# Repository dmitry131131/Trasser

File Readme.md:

# Трассерная насадка для игры в страйкбол

## Содержание
1. [Цель проекта](#цель-проекта)
2. [Режимы работы](#режимы-работы)
3. [Принцип работы](#принцип-работы)
4. [Необходимые компоненты](#необходимые-компоненты)
5. [Используемые инструменты и станки](#используемые-инструменты-и-станки)
6. [Проблемы и трудности](#проблемы-и-трудности)
7. [Результат](#результат)

## Цель проекта

Разработка и изготовление компактной и надежной трассерной насадки для страйкбольного оружия, которая позволяет визуализировать полет шаров в условиях низкой освещенности. Насадка будет крепиться на ствол оружия на резьбу `M14-` и активироваться при выстреле, подсвечивая траекторию полета шаров с помощью ультрафиолетовых светодиодов. Управление устройством осуществляется на базе микроконтроллера `ATtiny13`, что обеспечивает минимальные габариты и энергопотребление.

## Режимы работы

Трассерная насадка будет иметь `3 режима` работы:
1. Ультрафиолетовая вспышка для подсветки шаров
2. Оранжевая вспышка на срезе ствола для имитации вспышки выстрела
3. Ультрафиолетовая вспышка и имитация вспышки выстрела

## Принцип работы

+ При выстреле страйкбольный шар проходит через ствол, пересекая луч инфракрасного датчика.
+ Датчик передает сигнал на микроконтроллер ATtiny13.
+ Микроконтроллер активирует ультрафиолетовые светодиоды на короткий промежуток времени (0.1 секунду).
+ Светодиоды подсвечивают шар внутри ствола, делая его видимым в темноте.
+ После завершения цикла устройство возвращается в режим ожидания для экономии энергии.

### Идейная схема реализации 

## Необходимые компоненты

Список необходимых компонентов:

### Электроника

| Компонент                         | Количество             |
|-----------------------------------|------------------------|
| Двухсторонний текстолит           | 100x100mm              |
| Микроконтроллер Attiny13          | 1шт                    |
| УФ светодиоды формата 5050        | 3шт                    |
| Оранжевые светодиоды 1206         | 3шт                    |
| SMD переменный резистор 20k       | 1шт                    |
| SMD резистор 0805 10k             | 1шт                    |
| SMD резистор 0805 1k              | 4шт                    |
| SMD резистор 0805 4k              | 1шт                    |
| SMD резистор 1206 20ОМ            | 2шт                    |
| SMD резистор 1206 150ОМ           | 1шт                    |
| SMD транзистор NPN bc817-40       | 2шт                    |
| SMD конденсатор 0603 0.1мкФ       | 2шт                    |
| SMD конденсатор 0603 10мкФ        | 1шт                    |
| Инфракрасный фотодиод 3мм         | 1шт                    |
| SMD инфракрасный светодиод        | 1шт                    |
| SMD светодиод 0603 красный        | 1шт                    |
| SMD светодиод 0603 синий          | 1шт                    |
| SMD микросхема TP4056             | 1шт                    |
| Li-ion аккумулятор 20/20/4мм 3.7В | 1шт                    |
| USB Type-C разъём                 | 1шт                    |
| SMD кнопка                        | 1шт                    |

### Корпус

| Компонент                         | Количество             |
|-----------------------------------|------------------------|
| Алюминиевая труба D = 35мм        | 60мм                   |
| Прозрачная трубка D = 15мм        | 60мм                   |
| Винты M3 15мм                     | 2шт                    |
| Круг алюминиевый Д16-Т D = 40мм   | 60мм                   |
| Прокладка диаметром 15мм          | 1шт                    |
| Круг алюминиевый D = 20мм         | 30мм                   |

## Используемые инструменты и станки

В этом проекте было задействовано следующее оборудование:

### Для изготовления корпуса

Для изготовления корпуса и переходника `M11/M14-` были использованы:

1. Токарно-винторезный станок `JET GHB-1340A DRO` - для токарных работ

2. Редукторный фрезерно-сверлильный станок `JET JMD-45LPFD` - для фрезерно-сверлильных работ

3. Ленточнопильный станок `JET MBS-1011DAP` - для отрезания заготовок

### Для изготовления электроники

1. Настольный фрезерно-гравировальный станок `Charly 4U` - для изготовления печатных плат

2. Осцилограф цифровой `UNI TREND UTD2102CM` - для диагностики схемы

3. Паяльная станция `Ersa i-CON1` с паяльником `i-TOOL 0IC1100A` - для сборки печатной платы

## Процесс изготовления

#### Измерение всех стыковочных параметров, таких как характерные габариты, толщина ствола и параметры резьбы.
  В результате этих измерений было установлено, что в качестве основной резьбы крепления насадки к стволу служит левая резьба стандарта М14 шаг 1мм
  Но в качестве дополнения для использования на стволе пистолета решено было добавить в комплект переходник с M14- на резьбу M11 шаг 1мм, потому что
  именно такую резьбу имеет ствол пистолета.

#### Выбор материалов корпуса, соответствующих требованиям по прочности.
  Материалом корпуса должен был быть прочный металл, который легко выдерживает попадания страйкбольной пули.
  Из вариантов представляется сталь и алюминий. Сталь отбрасывается из-за своей массы и в итоге выбор падает на алюминий.

#### Разработка 3D моделей корпуса и внутреннего каркаса.
  После выбора материала и получения понимания о габаритах разрабатывается 3D модель корпуса в 5 основных деталях:
  + Передняя крышка
  + Основная труба
  + Задняя крышка
  + Внутренняя прозрачная трубка
  + Резьбовой переходник

#### Выбор микроконтроллера, датчиков и дополнительных компонентов.
  Выбор микроконтроллеров на текущий момент велик, но из-за полноты документации и низкой цены выбор пал на Attiny13 архитектуры AVR
  Это компактный 8-ми битный микроконтроллер, работающий на тактовой частоте от 1 до 20 MГц имеющий 6 портов ввода-вывода,
  встроенный аналоговый компаратор, таймер, развитую систему прерываний. Этих возможностей оказывается вполне достаточно для решения задачи.

  Датчик пролета шара основан на инфракрасном фотодиоде, который освещён инфракрасным светодиодом с противоположной стороны и при изменении освещённости
  напряжение на фотодиоде меняется и срабатывает компаратор.

#### Определение оптимальной схемы подключения датчиков.
  Путём экспериментов и постепенного изучения возможностей микроконтроллера была спроектирована и протестирована схема на макетной плате.
  После тестирования сборки можно было приступать к проектированию печатных плат.

#### Разработка принципиальной электрической схемы.
  Из-за необходимости использовать практически везде элементы поверхностного монтажа пришлось немного корректировать принципиальную схему
  исходя из фактических характеристик компонентов, например напряжение открытия транзистора.

#### Разработка и изготовление печатных плат.
  Проектирование печатных плат производилось в программе KICAD.
  После проектирования печатных плат требовалось их изготовить. Для этого использовался фрезерный ЧПУ станок `Charly 4U`.
  К тому же из-за необходимости изготавливать двухсторонние печатные платы пришлось придумывать технологию для соотнесения переходных отверстий.
  Суть метода заключается в том, чтобы просверлить в печатной плате симметрично 4 отверстия под концелярские кнопки и при перевороте платы соотносить эти 4 отверстия.

#### Изготовление и сборка корпуса, финальная сборка.
  После изготовления печатных плат нужно было произвести сборку, распаять все компоненты, прошить микроконтроллер, собрать все в корпус.
  Также необходимо было произвести тесты всех частей устройства.

#### Испытания в лабораторных и боевых условиях.
  Финальной стадией стало тестирование реакции устройства в штатом режиме, тестирование переключения режимов, тестирование модуля зарядки аккумулятора,
  а также тестирование непосредственно в работе.

## Проблемы и трудности

В процессе изготовления возникли некоторые трудности, которые пришлось преодолеть

### Неисправность токарного станка

Первой проблемой, которую необходимо было решить это неисправность ходового винта токарного станка. Так как мне было необходимо нарезать нестандартную резьбу, мне нужен был функционирующий ходовой винт на токарном станке, но он был повреждён предыдущими пользователями(срезаны срезные шпильки крепления).

Для решения этой проблемы с помощью другого токарного станка(без возможности нарезания резьбы) `MetalMaster MML2870M` были выточены новые срезные шпильки из латуни и функционирование токарного станка `JET GHB-1340A DRO` было восстановлено.

### Необходимость нарезания резьбы по алюминию

Процесс нарезания резьбы по алюминию представляет некоторую трудность из-за пластичности металла, поэтому если использовать универсальные резьбонарезные пластинки, то резьба получается рваная, вот пример:

Поэтому были куплены специальные резьбонарезные пластинки по алюминию(сплав К15) и результат был сильно улучшен, вот пример:

### Необходимость создания двухсторонних печатных плат

В виду компактности печатной платы имеется необходимость размещения компонентов и дорожек на двух поверхностях печатной платы.
Но на фрезерном станке удобно производить односторонние печальные платы, в результате чего мною использована технология по точному совпадению печатной платы при перевороте по 4 точкам, чтобы добиться соосности переходных отверстий. 

`Процесс фрезеровки:`

<video width="600" height="800" controls>
  <source src="img/Фрезировка.mp4" type="video/mp4">
</video>

### Несовпадение габаритов фотодиода

Габариты фотодиода оказались больше ожидаемых, в результате чего он не помещался под прозрачной трубкой.

Пришлось с помощью гравера уменьшить его габариты:

## Тестирование

После предварительной сборки устройства без системы зарядки аккумулятора был произведён тест на срабатывание датчика и включение вспышки.
Также был произведён тест смены режимов работы(посредством удержания кнопки на корпусе в течение 1 секунды). 
Индикатором смены режима работы служит кратковременная вспышка на торце насадки.

### Срабатывание датчика в замедленной съёмке
<video width="600" height="800" controls>
  <source src="img/Слоумо.mp4" type="video/mp4">
</video>

Затем был произведён тест работы модуля зарядки. При зарядке загорается индикация и идет процесс зарядки. 

### Работа индикации заряда аккумулятора

Затем после финальной сборки изделия был произведён финальный тест непосредственно в условиях эксплуатации.

### Работа насадки
<video width="600" height="800" controls>
  <source src="img/Выстрел.mp4" type="video/mp4">
</video>

## Результат

В результате получилась полностью рабочая и готовая к эксплуатации трассерная насадка.

Но в процессе тестирования была выявлена одна незначительная ошибка:

При сборке были перепутаны красный и синий светодиоды в модуле зарядки. 
И теперь в процессе зарядки горит синий светодиод, а индикатор заряженного аккумулятора горит красным цветом.

Но эта ошибка не влияет на основную задачу насадки.

|                       |                             |                                    |
| ---------------------------------------------------------- | ------------------------------------------------------------- | ------------------------------------------- |
|  |  |

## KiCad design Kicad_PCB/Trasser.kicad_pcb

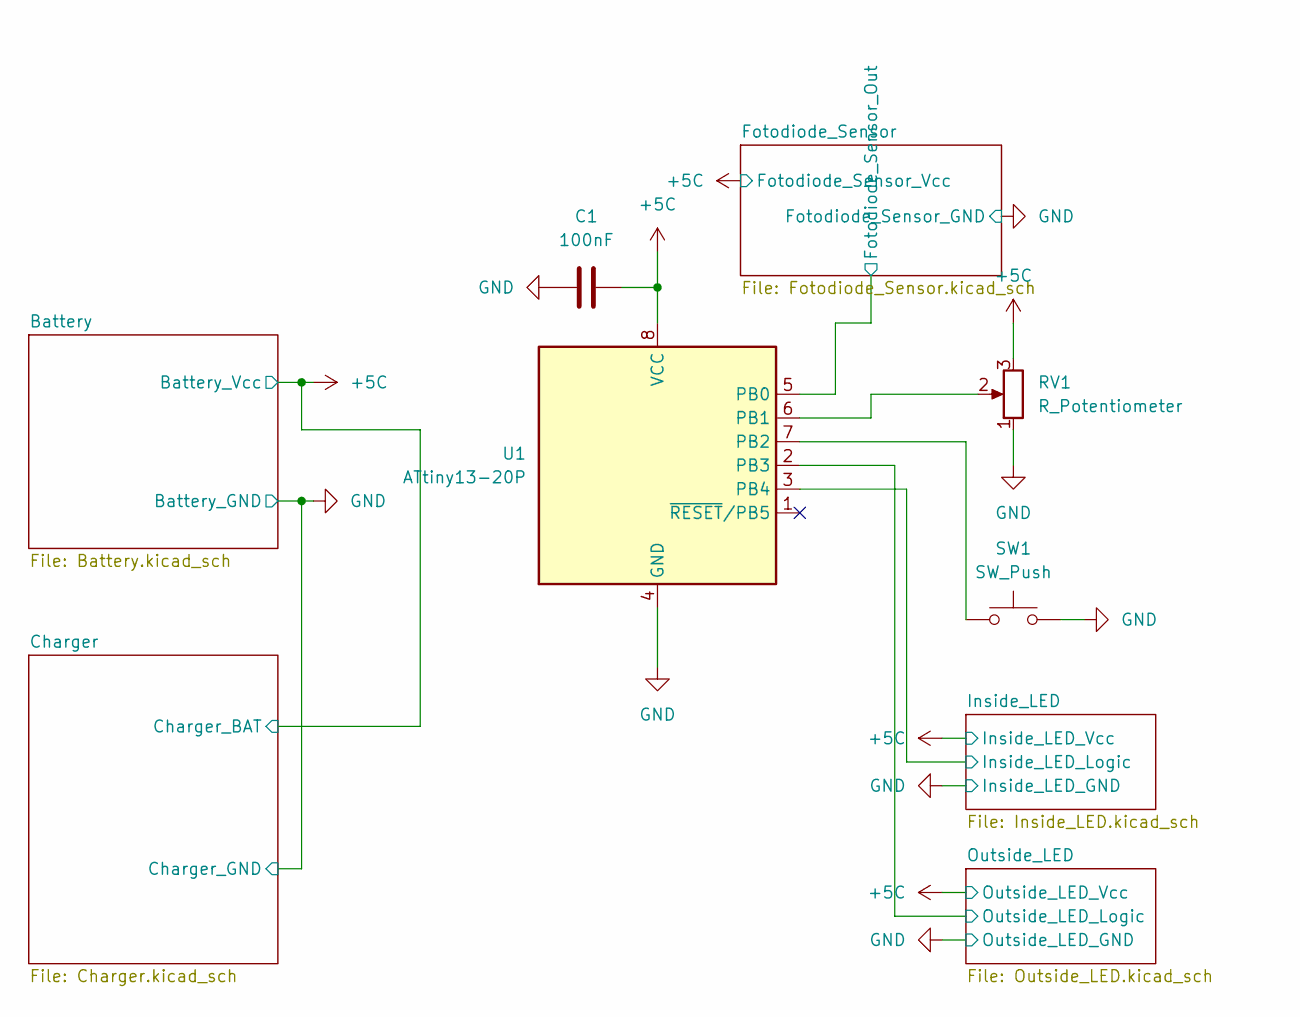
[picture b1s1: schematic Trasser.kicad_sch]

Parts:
C1: 100nF; C_0603_1608Metric_Pad1.08x0.95mm_HandSolder
RV1: R_Potentiometer; Potentiometer_Bourns_TC33X_Vertical
SW1: SW_Push; SW_SPST_EVQPE1
U1: ATtiny13-20P; DIP-8_W7.62mm

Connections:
+5C: C1.2, RV1.3, U1.8 (VCC); also elsewhere on the board
/Fotodiode_Sensor/Fotodiode_Sensor_Out: U1.5 (PB0); also elsewhere on the board
/Inside_LED/Inside_LED_Logic: U1.3 (PB4); also elsewhere on the board
/Outside_LED/Outside_LED_Logic: U1.2 (PB3); also elsewhere on the board
GND: C1.1, RV1.1, SW1.2, U1.4 (GND); also elsewhere on the board
unnamed: RV1.2, U1.6 (PB1)
unnamed: SW1.1, U1.7 (PB2)

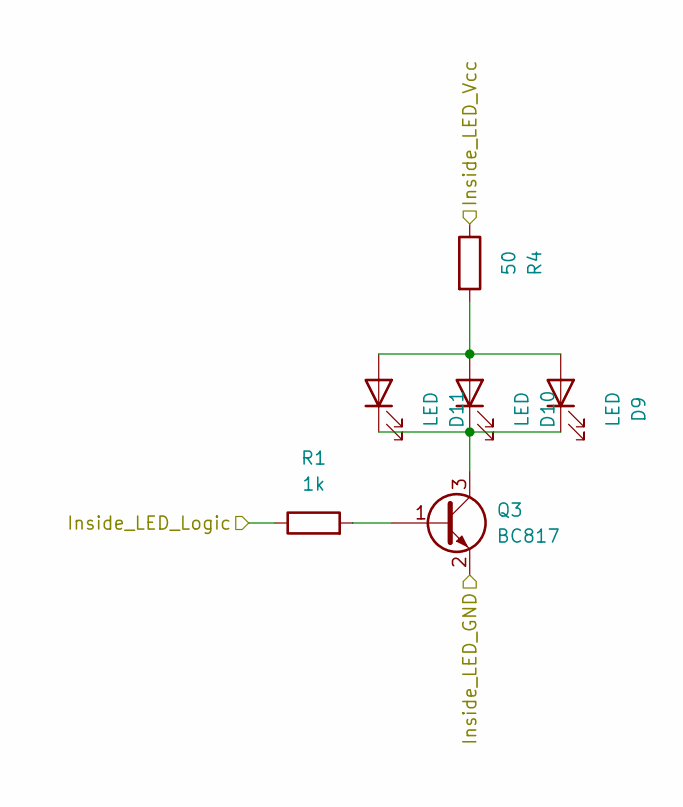
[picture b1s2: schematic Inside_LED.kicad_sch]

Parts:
D9, D10, D11: LED; LED_5050
Q3: BC817; SOT-23
R1: 1k; R_0603_1608Metric
R4: 50; R_1206_3216Metric

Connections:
+5C: R4.1; also elsewhere on the board
/Inside_LED/Inside_LED_Logic: R1.1; also elsewhere on the board
GND: Q3.2 (E); also elsewhere on the board
unnamed: D9.2 (A), D10.2 (A), D11.2 (A), R4.2
unnamed: D9.1 (K), D10.1 (K), D11.1 (K), Q3.3 (C)
unnamed: Q3.1 (B), R1.2

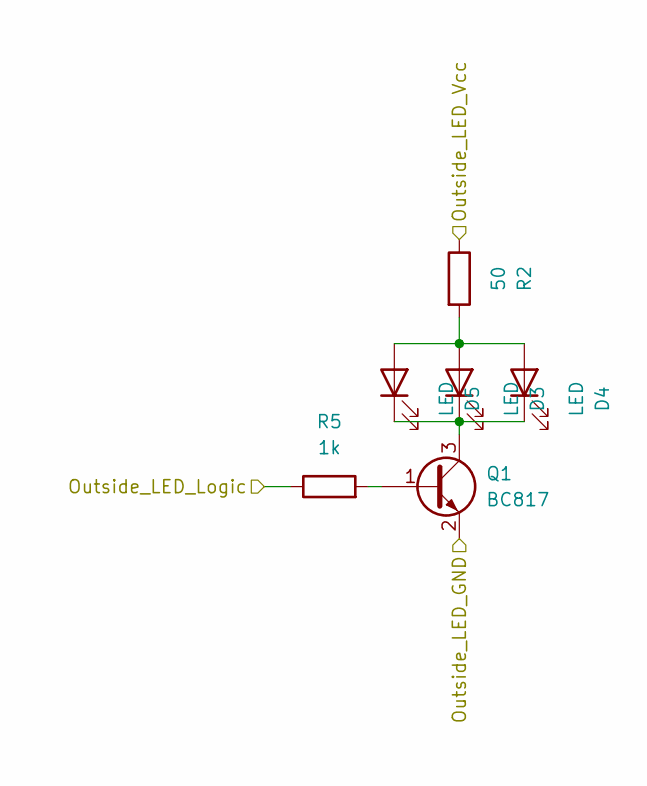
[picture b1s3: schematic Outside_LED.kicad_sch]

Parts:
D3, D4, D5: LED; LED_1206_3216Metric
Q1: BC817; SOT-23
R2: 50; R_1206_3216Metric
R5: 1k; R_0603_1608Metric

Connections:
+5C: R2.1; also elsewhere on the board
/Outside_LED/Outside_LED_Logic: R5.1; also elsewhere on the board
GND: Q1.2 (E); also elsewhere on the board
unnamed: D3.2 (A), D4.2 (A), D5.2 (A), R2.2
unnamed: D3.1 (K), D4.1 (K), D5.1 (K), Q1.3 (C)
unnamed: Q1.1 (B), R5.2

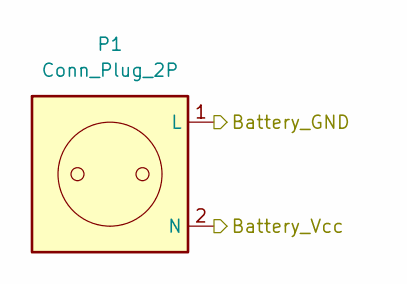
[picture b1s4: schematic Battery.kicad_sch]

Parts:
P1: Conn_Plug_2P; PinSocket_1x02_P2.00mm_Horizontal

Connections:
+5C: P1.2 (N); also elsewhere on the board
GND: P1.1 (L); also elsewhere on the board

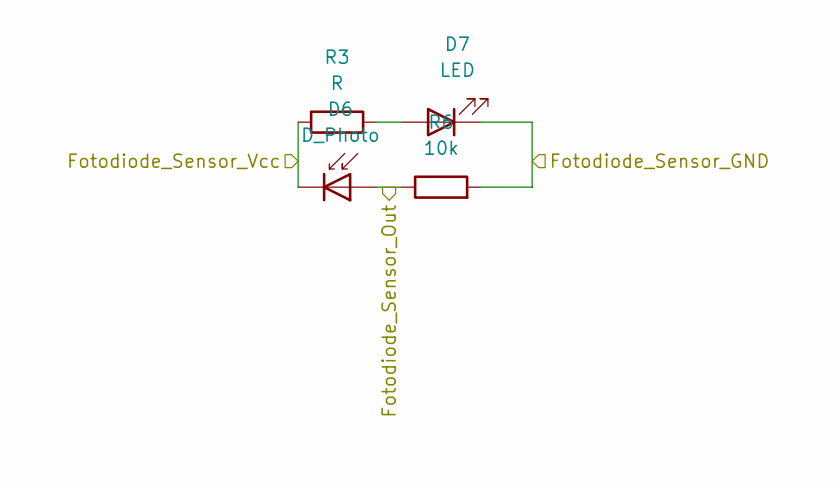
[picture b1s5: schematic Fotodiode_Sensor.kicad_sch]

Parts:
D6: D_Photo; LED_D3.0mm
D7: LED; LED_PLCC_2835_Handsoldering
R3: R; R_1206_3216Metric
R6: 10k; R_0805_2012Metric_Pad1.20x1.40mm_HandSolder

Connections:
+5C: D6.1 (K), R3.1; also elsewhere on the board
/Fotodiode_Sensor/Fotodiode_Sensor_Out: D6.2 (A), R6.1; also elsewhere on the board
GND: D7.1 (K), R6.2; also elsewhere on the board
unnamed: D7.2 (A), R3.2

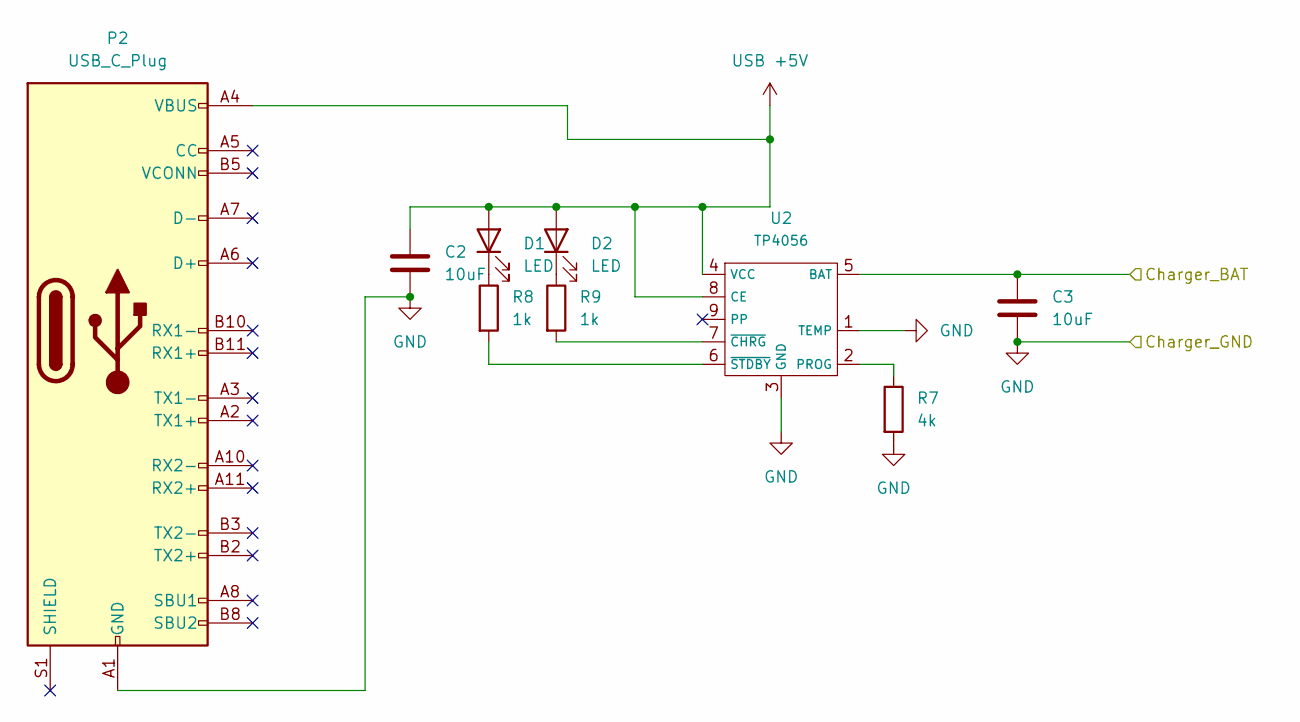
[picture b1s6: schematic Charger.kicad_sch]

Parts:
C2, C3: 10uF; C_0603_1608Metric_Pad1.08x0.95mm_HandSolder
D1, D2: LED; LED_0402_1005Metric
P2: USB_C_Plug; USB_C_POWER_ONLY
R7: 4k; R_0603_1608Metric_Pad0.98x0.95mm_HandSolder
R8, R9: 1k; R_0805_2012Metric_Pad1.20x1.40mm_HandSolder
U2: TP4056; SOIC-8-1EP_3.9x4.9mm_P1.27mm_EP2.29x3mm

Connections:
+5C: C3.1, U2.5 (BAT); also elsewhere on the board
GND: C2.2, C3.2, P2.A1 (GND), P2.A12 (GND), P2.B1 (GND), P2.B12 (GND), R7.2, U2.1 (TEMP), U2.3 (GND); also elsewhere on the board
unnamed: D1.1 (K), R8.1
unnamed: D2.1 (K), R9.1
unnamed: R7.1, U2.2 (PROG)
unnamed: R9.2, U2.7 (~CHRG)
unnamed: R8.2, U2.6 (~STDBY)
USB +5V: C2.1, D1.2 (A), D2.2 (A), P2.A4 (VBUS), P2.A9 (VBUS), P2.B4 (VBUS), P2.B9 (VBUS), U2.4 (VCC), U2.8 (CE)

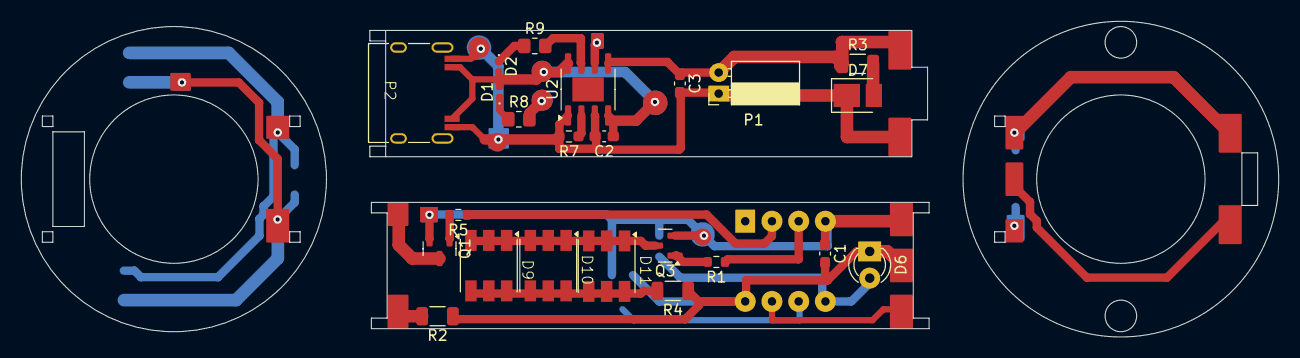
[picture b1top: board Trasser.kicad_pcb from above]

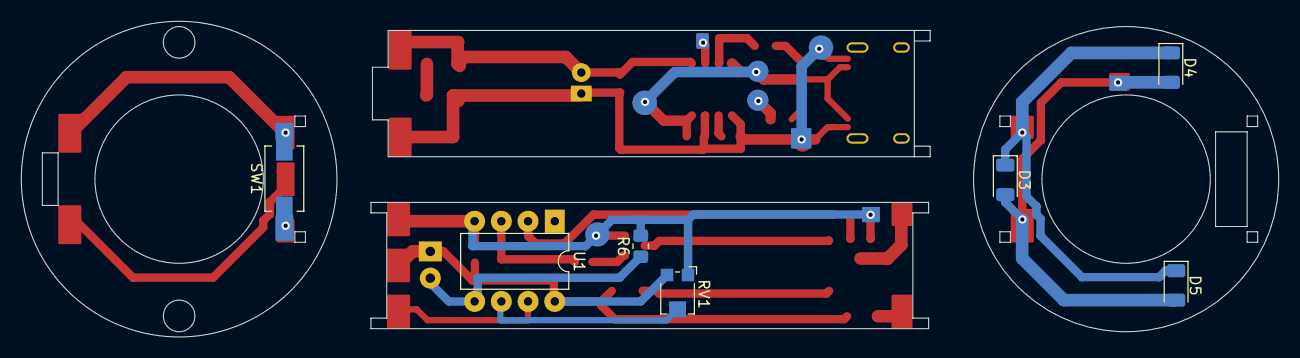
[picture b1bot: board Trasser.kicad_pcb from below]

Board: 2 copper layers, 119.5 x 30.0 mm, 30 parts (7 on the bottom side), 20 nets.

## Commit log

2025-03-13 Added 3D models and designs
2025-03-13 Added readme
2025-03-13 Added PCB and Electric Schemes
2025-03-15 Added code to repo with readme for code
2025-03-16 Added video and photo and made readme
2025-03-18 Added new topic in readme
2025-03-18 Fixed links to videos
2025-03-19 Added more images and video
2025-06-07 [Code] Made writing high frequency fuses and fixed custom_delay function
2025-06-08 [UPT] Made power control with watchdog timer and Additional transistor on PB0
